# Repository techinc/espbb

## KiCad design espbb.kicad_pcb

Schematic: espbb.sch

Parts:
C1, C2: C
P1, P2: CONN_8
R1, R2: R
SW1: SWITCH_INV
U1: ESP-12/07V2/08V2
U2: LM6206; SOT23

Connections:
3V3: C1.1, R1.2, U1.8, U2.2 (OUT)
GND: C1.2, C2.2, P2.1, R2.2, SW1.3, U1.9, U2.1 (GND)
unnamed: P2.8, U1.16
unnamed: P2.7, U1.15
unnamed: P2.6, U1.14
unnamed: P2.5, U1.13
unnamed: P2.4, SW1.2, U1.12
unnamed: P2.3, U1.11
unnamed: P2.2, R2.1, U1.10
unnamed: P1.7, U1.7
unnamed: P1.6, U1.6
unnamed: P1.5, U1.5
unnamed: P1.4, U1.4
unnamed: P1.3, R1.1, U1.3
unnamed: P1.2, U1.2
unnamed: P1.1, U1.1
VCC: C2.1, P1.8, U2.3 (IN)

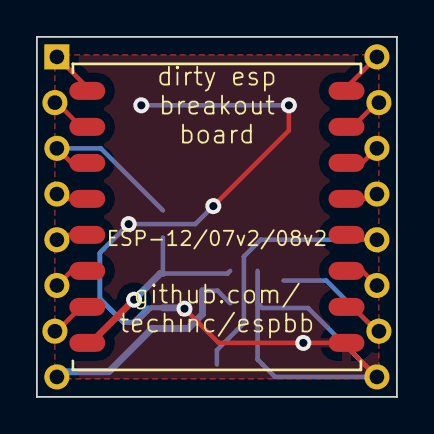
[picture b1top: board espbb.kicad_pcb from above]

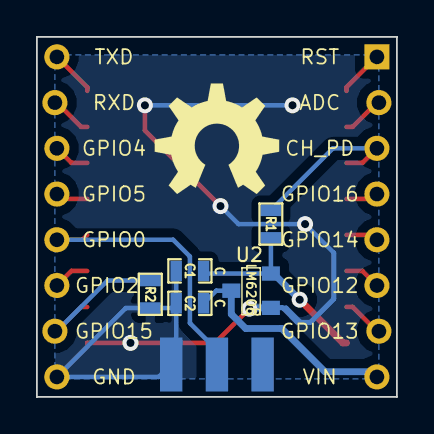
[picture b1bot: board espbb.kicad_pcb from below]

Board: 2 copper layers, 20.0 x 20.0 mm, 9 parts (6 on the bottom side), 17 nets.

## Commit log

2015-03-30 fix DRC warnings
2015-03-30 change gpio number
